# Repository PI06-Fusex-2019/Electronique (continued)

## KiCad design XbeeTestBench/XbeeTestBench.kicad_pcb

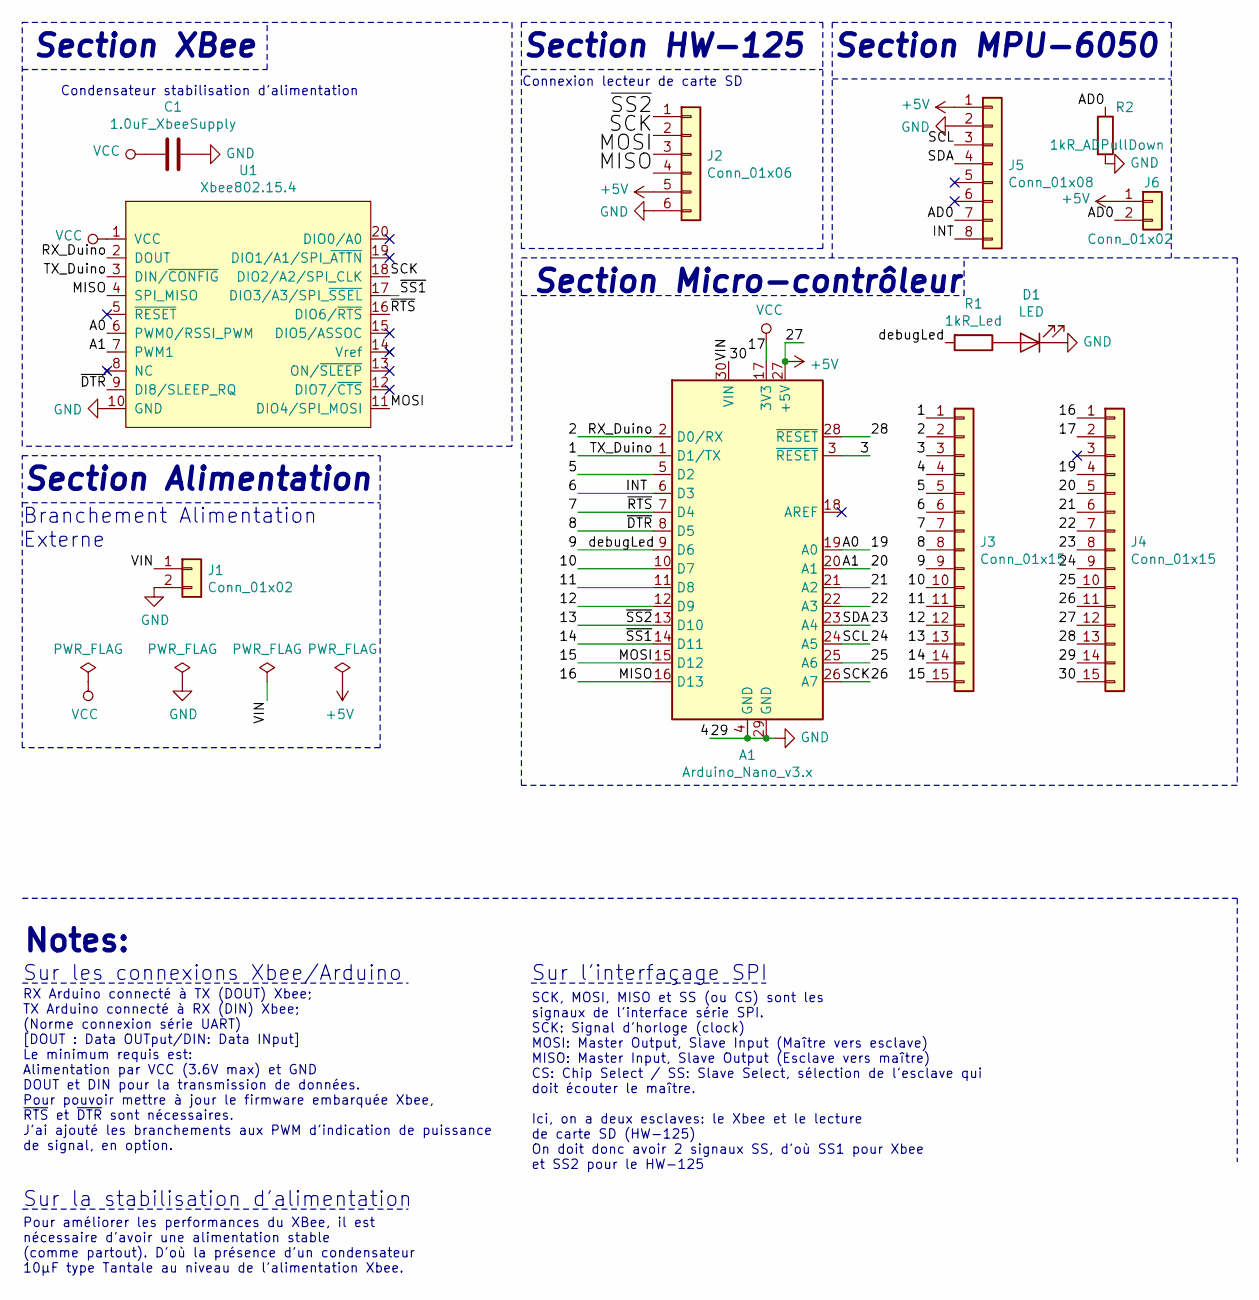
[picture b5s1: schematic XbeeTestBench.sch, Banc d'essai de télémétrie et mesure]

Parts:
A1: Arduino_Nano_v3.x; Arduino_Nano
C1: 1.0uF_XbeeSupply; C_1206_3216Metric_Pad1.42x1.75mm_HandSolder
D1: LED; LED_D5.0mm
J1: Conn_01x02; BatConn
J2: Conn_01x06; PinHeader_1x06_P2.54mm_Vertical
J3, J4: Conn_01x15; PinHeader_1x15_P2.54mm_Vertical
J5: Conn_01x08; PinSocket_1x08_P2.54mm_Vertical
J6: Conn_01x02; PinSocket_1x02_P2.54mm_Horizontal
R1: 1kR_Led; R_1206_3216Metric_Pad1.42x1.75mm_HandSolder
R2: 1kR_ADPullDown; R_1206_3216Metric_Pad1.42x1.75mm_HandSolder
U1: Xbee802.15.4; XBEE-20_THT

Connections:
+5V: A1.27 (+5V), J2.5, J4.12, J5.1, J6.1
/1: A1.1 (D1/TX), J3.1, U1.3 (DIN/~CONFIG)
/2: A1.2 (D0/RX), J3.2, U1.2 (DOUT)
/3: A1.3 (~RESET), J3.3
/5: A1.5 (D2), J3.5
/6: A1.6 (D3), J3.6, J5.8
/7: A1.7 (D4), J3.7, U1.16 (DIO6/~RTS)
/8: A1.8 (D5), J3.8, U1.9 (DI8/SLEEP_RQ)
/9: A1.9 (D6), J3.9, R1.2
/10: A1.10 (D7), J3.10
/11: A1.11 (D8), J3.11
/12: A1.12 (D9), J3.12
/13: A1.13 (D10), J2.1, J3.13
/14: A1.14 (D11), J3.14, U1.17 (DIO3/A3/SPI_~SSEL)
/15: A1.15 (D12), J2.3, J3.15, U1.11 (DIO4/SPI_MOSI)
/16: A1.16 (D13), J2.4, J4.1, U1.4 (SPI_MISO)
/19: A1.19 (A0), J4.4, U1.6 (PWM0/RSSI_PWM)
/20: A1.20 (A1), J4.5, U1.7 (PWM1)
/21: A1.21 (A2), J4.6
/22: A1.22 (A3), J4.7
/23: A1.23 (A4), J4.8, J5.4
/24: A1.24 (A5), J4.9, J5.3
/25: A1.25 (A6), J4.10
/26: A1.26 (A7), J2.2, J4.11, U1.18 (DIO2/A2/SPI_CLK)
/28: A1.28 (~RESET), J4.13
/30: A1.30 (VIN), J1.1, J4.15
/AD0: J5.7, J6.2, R2.1
GND: A1.4 (GND), A1.29 (GND), C1.1, D1.1 (K), J1.2, J2.6, J3.4, J4.14, J5.2, R2.2, U1.10 (GND)
unnamed: D1.2 (A), R1.1
VCC: A1.17 (3V3), C1.2, J4.2, U1.1 (VCC)

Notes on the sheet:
RX Arduino connecté à TX (DOUT) Xbee; TX Arduino connecté à RX (DIN) Xbee; (Norme connexion série UART) [DOUT : Data OUTput/DIN: Data INput] Le minimum requis est: Alimentation par VCC (3.6V max) et GND DOUT et DIN pour la transmission de données. Pour pouvoir mettre à jour le firmware embarquée Xb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
Sur les connexions Xbee/Arduino
Notes:
Pour améliorer les performances du XBee, il est nécessaire d'avoir une alimentation stable (comme partout). D'où la présence d'un condensateur 10µF type Tantale au niveau de l'alimentation Xbee.
Sur la stabilisation d'alimentation
Condensateur stabilisation d'alimentation
Branchement Alimentation Externe
Sur l'interfaçage SPI
SCK, MOSI, MISO et SS (ou CS) sont les signaux de l'interface série SPI. SCK: Signal d'horloge (clock) MOSI: Master Output, Slave Input (Maître vers esclave) MISO: Master Input, Slave Output (Esclave vers maître) CS: Chip Select / SS: Slave Select, sélection de l'esclave qui doit écouter le maître.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
Section XBee
Section HW-125
Connexion lecteur de carte SD
Section Alimentation
Section Micro-contrôleur
Section MPU-6050

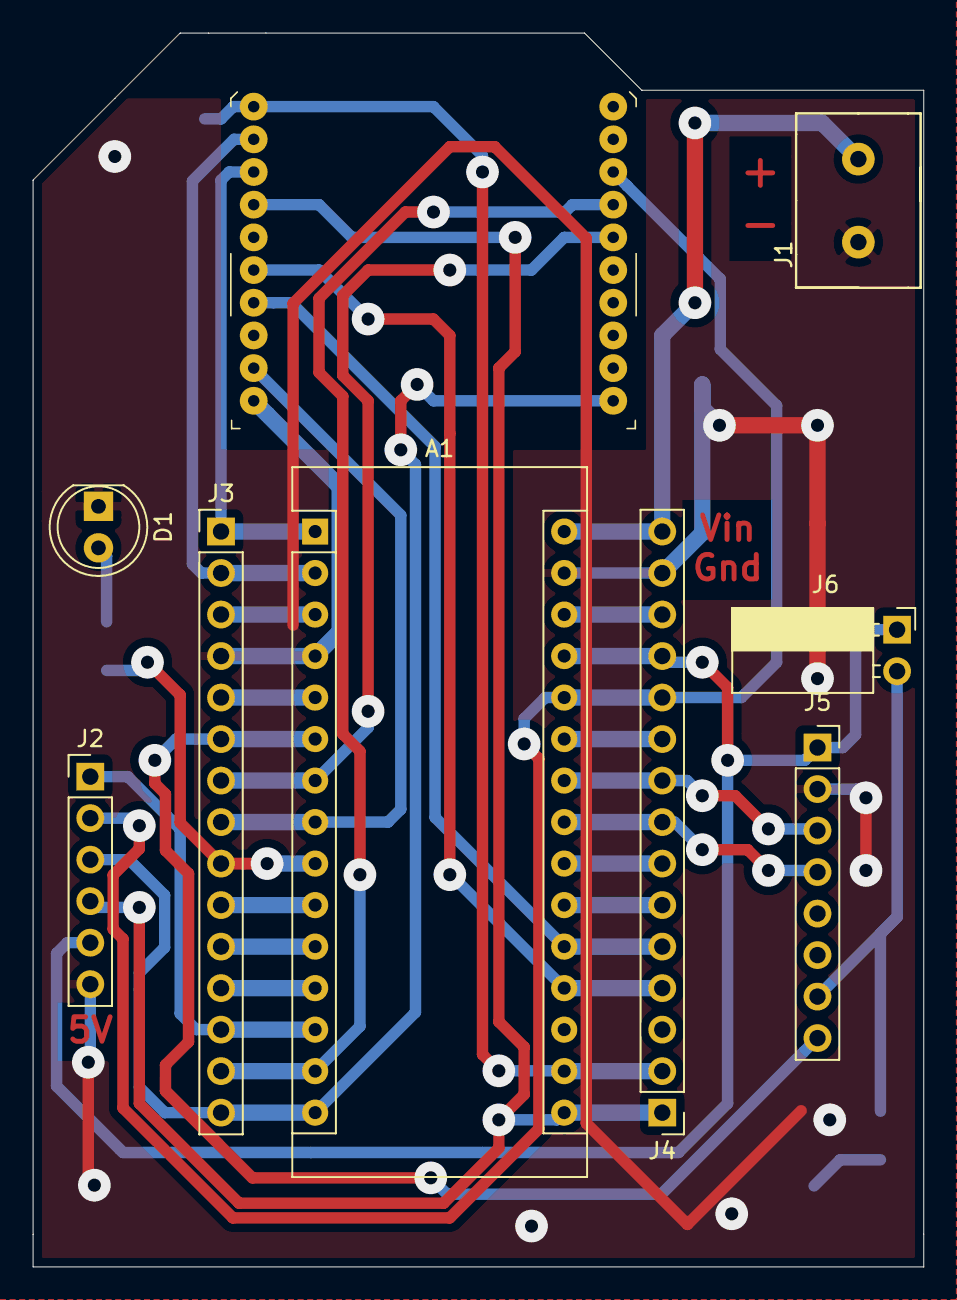
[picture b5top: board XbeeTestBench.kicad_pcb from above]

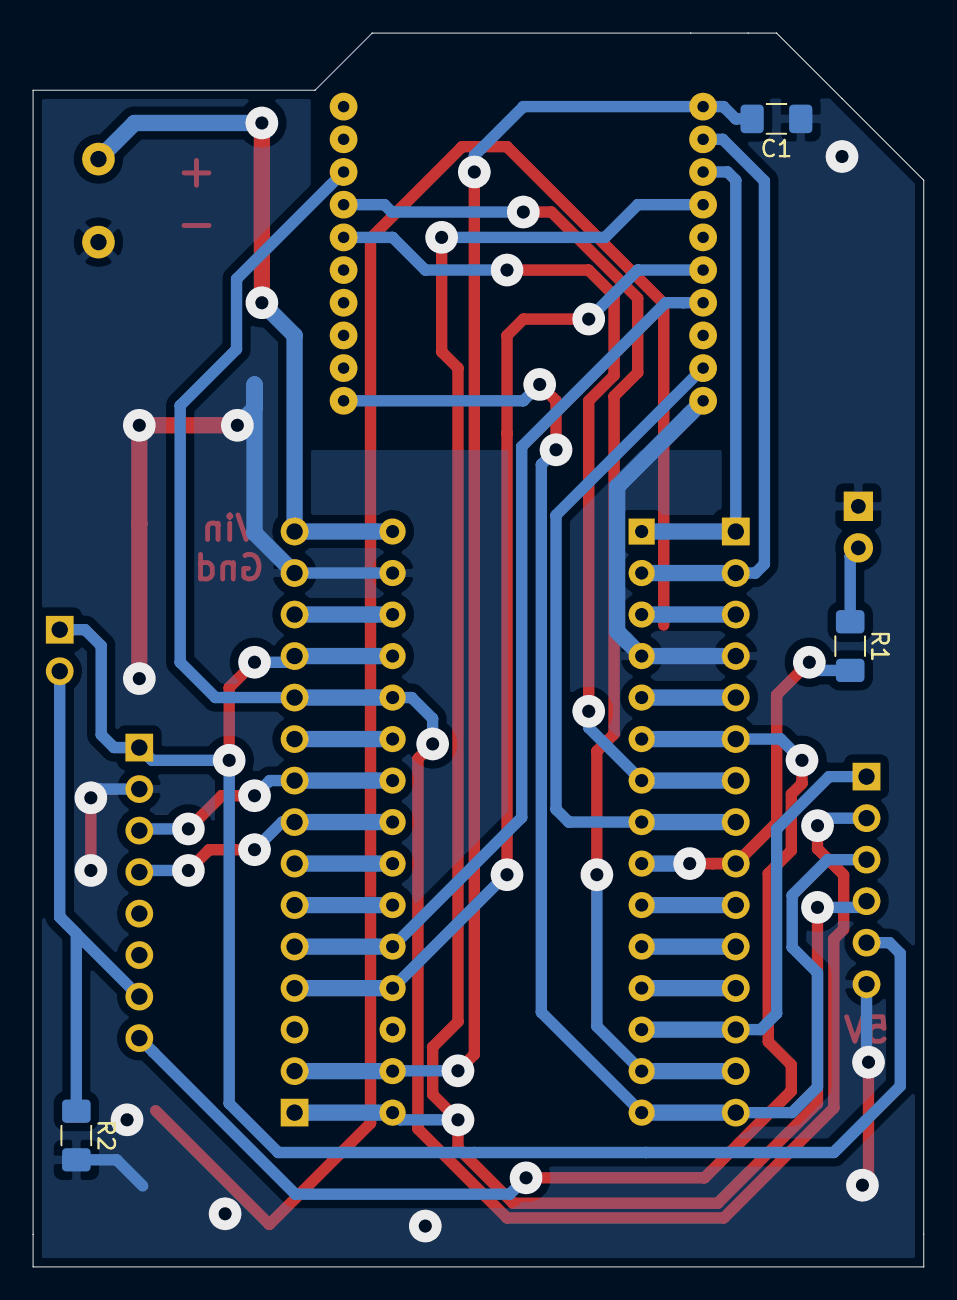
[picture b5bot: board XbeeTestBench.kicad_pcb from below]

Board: 2 copper layers, 54.5 x 75.5 mm, 12 parts (3 on the bottom side), 30 nets.

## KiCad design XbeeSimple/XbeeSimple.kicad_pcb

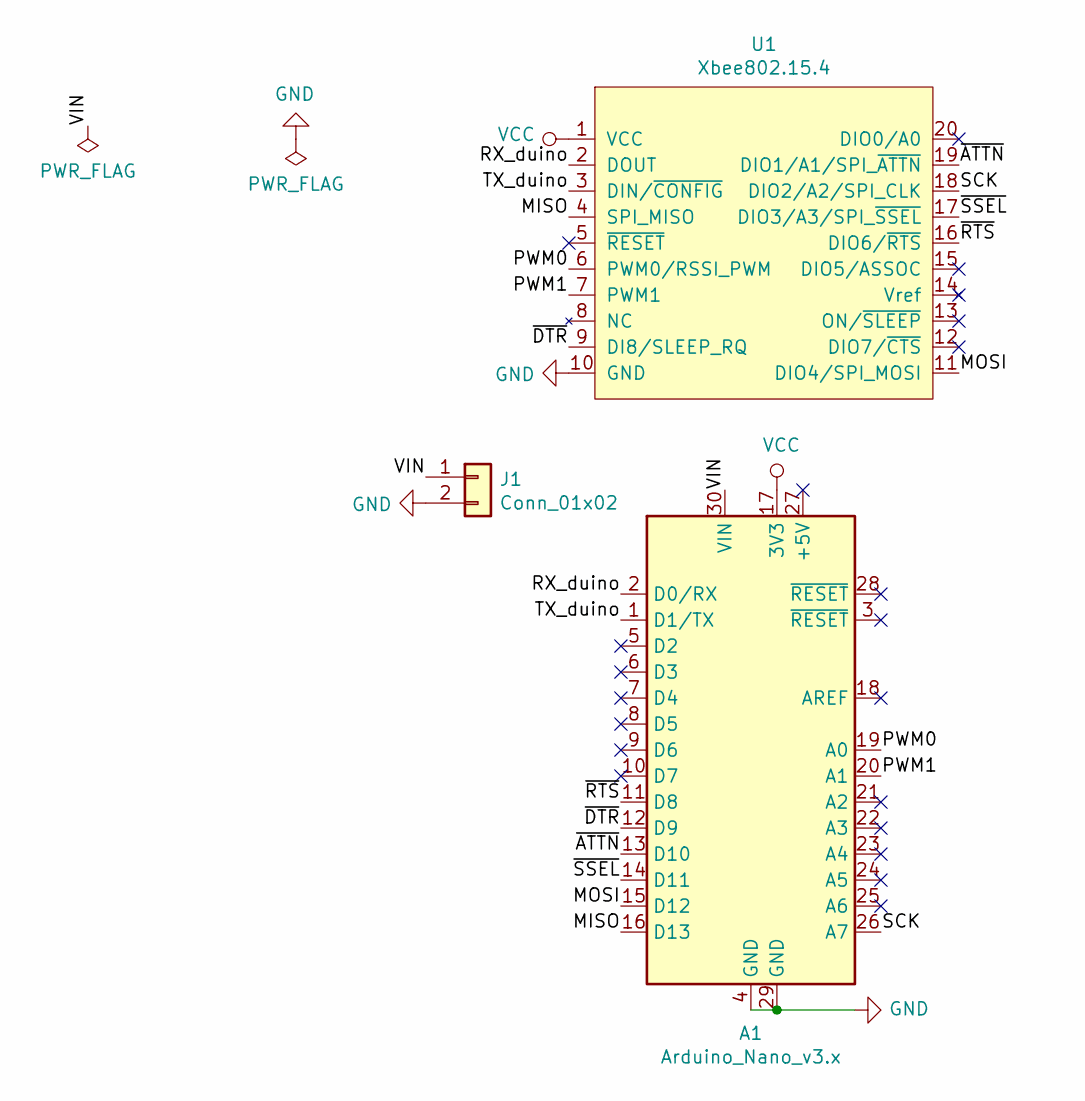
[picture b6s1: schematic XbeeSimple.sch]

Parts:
A1: Arduino_Nano_v3.x; Arduino_Nano
J1: Conn_01x02; BatConn
U1: Xbee802.15.4; XBEE-20_THT

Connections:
/MISO: A1.16 (D13), U1.4 (SPI_MISO)
/MOSI: A1.15 (D12), U1.11 (DIO4/SPI_MOSI)
/PWM0: A1.19 (A0), U1.6 (PWM0/RSSI_PWM)
/PWM1: A1.20 (A1), U1.7 (PWM1)
/RX_duino: A1.2 (D0/RX), U1.2 (DOUT)
/SCK: A1.26 (A7), U1.18 (DIO2/A2/SPI_CLK)
/TX_duino: A1.1 (D1/TX), U1.3 (DIN/~CONFIG)
/VIN: A1.30 (VIN), J1.1
/~ATTN: A1.13 (D10), U1.19 (DIO1/A1/SPI_~ATTN)
/~DTR: A1.12 (D9), U1.9 (DI8/SLEEP_RQ)
/~RTS: A1.11 (D8), U1.16 (DIO6/~RTS)
/~SSEL: A1.14 (D11), U1.17 (DIO3/A3/SPI_~SSEL)
GND: A1.4 (GND), A1.29 (GND), J1.2, U1.10 (GND)
VCC: A1.17 (3V3), U1.1 (VCC)

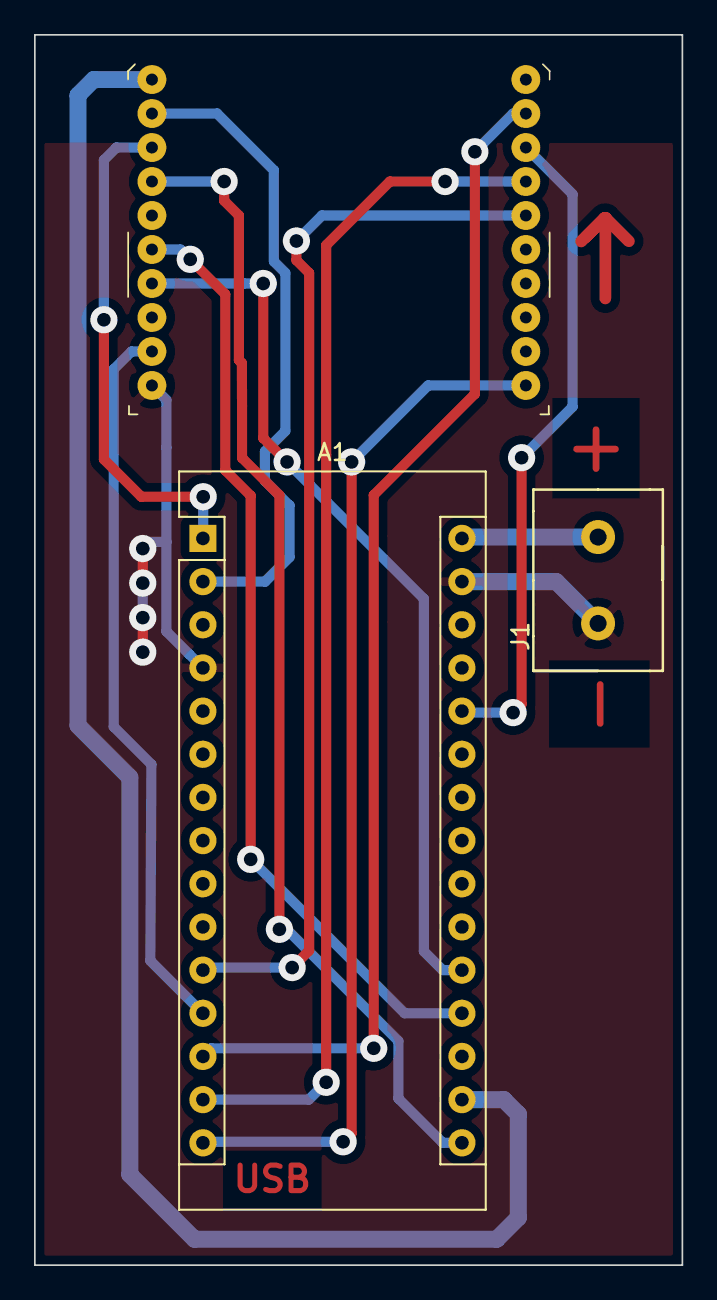
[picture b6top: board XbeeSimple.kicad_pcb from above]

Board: 2 copper layers, 38.1 x 72.4 mm, 3 parts (0 on the bottom side), 14 nets.

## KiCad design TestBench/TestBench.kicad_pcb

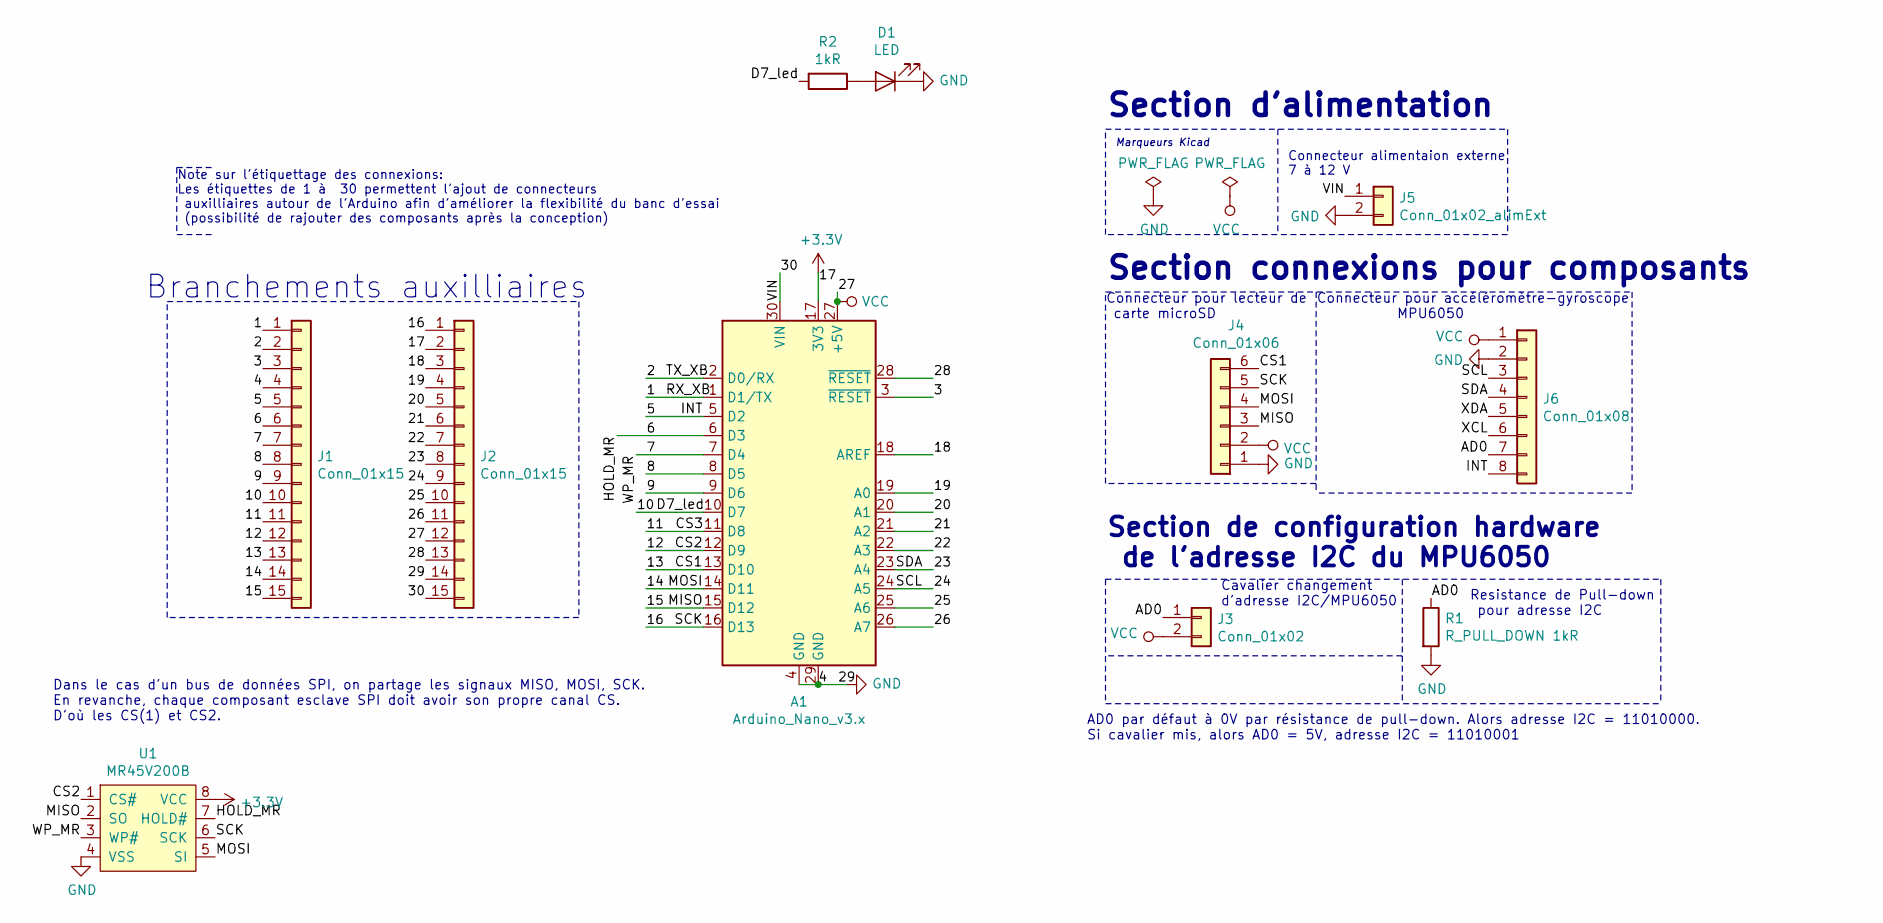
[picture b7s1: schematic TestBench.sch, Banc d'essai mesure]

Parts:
A1: Arduino_Nano_v3.x; Arduino_Nano
D1: LED; LED_D5.0mm
J1, J2: Conn_01x15; PinHeader_1x15_P2.54mm_Vertical
J3: Conn_01x02; PinHeader_1x02_P2.54mm_Vertical
J4: Conn_01x06; PinHeader_1x06_P2.54mm_Vertical
J5: Conn_01x02_alimExt; BatConn
J6: Conn_01x08; PinHeader_1x08_P2.54mm_Vertical
R1: R_PULL_DOWN 1kR; R_1206_3216Metric_Pad1.42x1.75mm_HandSolder
R2: 1kR; R_1206_3216Metric_Pad1.42x1.75mm_HandSolder
U1: MR45V200B; DIP-8_W7.62mm_LongPads

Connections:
+3V3: A1.17 (3V3), J2.2, U1.8 (VCC)
/1: A1.1 (D1/TX), J1.1
/2: A1.2 (D0/RX), J1.2
/3: A1.3 (~RESET), J1.3
/5: A1.5 (D2), J1.5, J6.8
/6: A1.6 (D3), J1.6, U1.7 (HOLD#)
/7: A1.7 (D4), J1.7, U1.3 (WP#)
/8: A1.8 (D5), J1.8
/9: A1.9 (D6), J1.9
/10: A1.10 (D7), J1.10, R2.2
/11: A1.11 (D8), J1.11
/12: A1.12 (D9), J1.12, U1.1 (CS#)
/13: A1.13 (D10), J1.13, J4.6
/14: A1.14 (D11), J1.14, J4.4, U1.5 (SI)
/15: A1.15 (D12), J1.15, J4.3, U1.2 (SO)
/16: A1.16 (D13), J2.1, J4.5, U1.6 (SCK)
/18: A1.18 (AREF), J2.3
/19: A1.19 (A0), J2.4
/20: A1.20 (A1), J2.5
/21: A1.21 (A2), J2.6
/22: A1.22 (A3), J2.7
/23: A1.23 (A4), J2.8, J6.4
/24: A1.24 (A5), J2.9, J6.3
/25: A1.25 (A6), J2.10
/26: A1.26 (A7), J2.11
/28: A1.28 (~RESET), J2.13
/30: A1.30 (VIN), J2.15, J5.1
/AD0: J3.1, J6.7, R1.1
/XCL: J6.6
/XDA: J6.5
GND: A1.4 (GND), A1.29 (GND), D1.1 (K), J1.4, J2.14, J4.1, J5.2, J6.2, R1.2, U1.4 (VSS)
unnamed: D1.2 (A), R2.1
VCC: A1.27 (+5V), J2.12, J3.2, J4.2, J6.1

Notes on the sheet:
Resistance de Pull-down pour adresse I2C
Cavalier changement d'adresse I2C/MPU6050
Section de configuration hardware de l'adresse I2C du MPU6050
AD0 par défaut à 0V par résistance de pull-down. Alors adresse I2C = 11010000. Si cavalier mis, alors AD0 = 5V, adresse I2C = 11010001
Connecteur pour accéléromètre-gyroscope MPU6050
Connecteur pour lecteur de carte microSD
Section connexions pour composants
Connecteur alimentaion externe 7 à 12 V
Marqueurs Kicad
Section d'alimentation
Note sur l'étiquettage des connexions: Les étiquettes de 1 à 30 permettent l'ajout de connecteurs auxilliaires autour de l'Arduino afin d'améliorer la flexibilité du banc d'essai (possibilité de rajouter des composants après la conception)
Branchements auxilliaires
Dans le cas d'un bus de données SPI, on partage les signaux MISO, MOSI, SCK. En revanche, chaque composant esclave SPI doit avoir son propre canal CS. D'où les CS(1) et CS2.

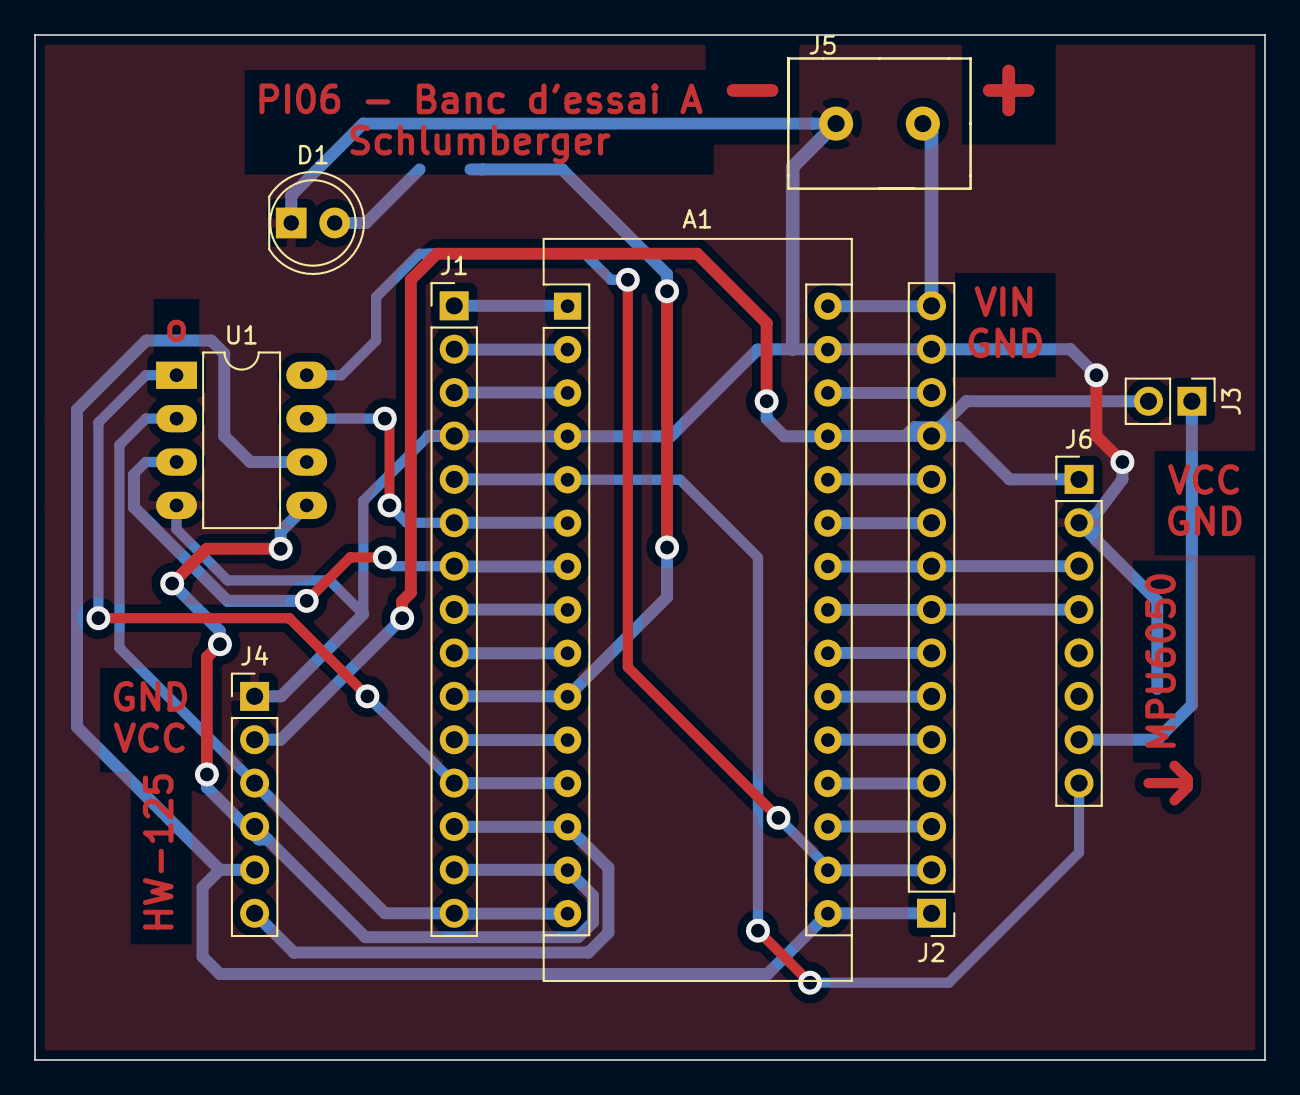
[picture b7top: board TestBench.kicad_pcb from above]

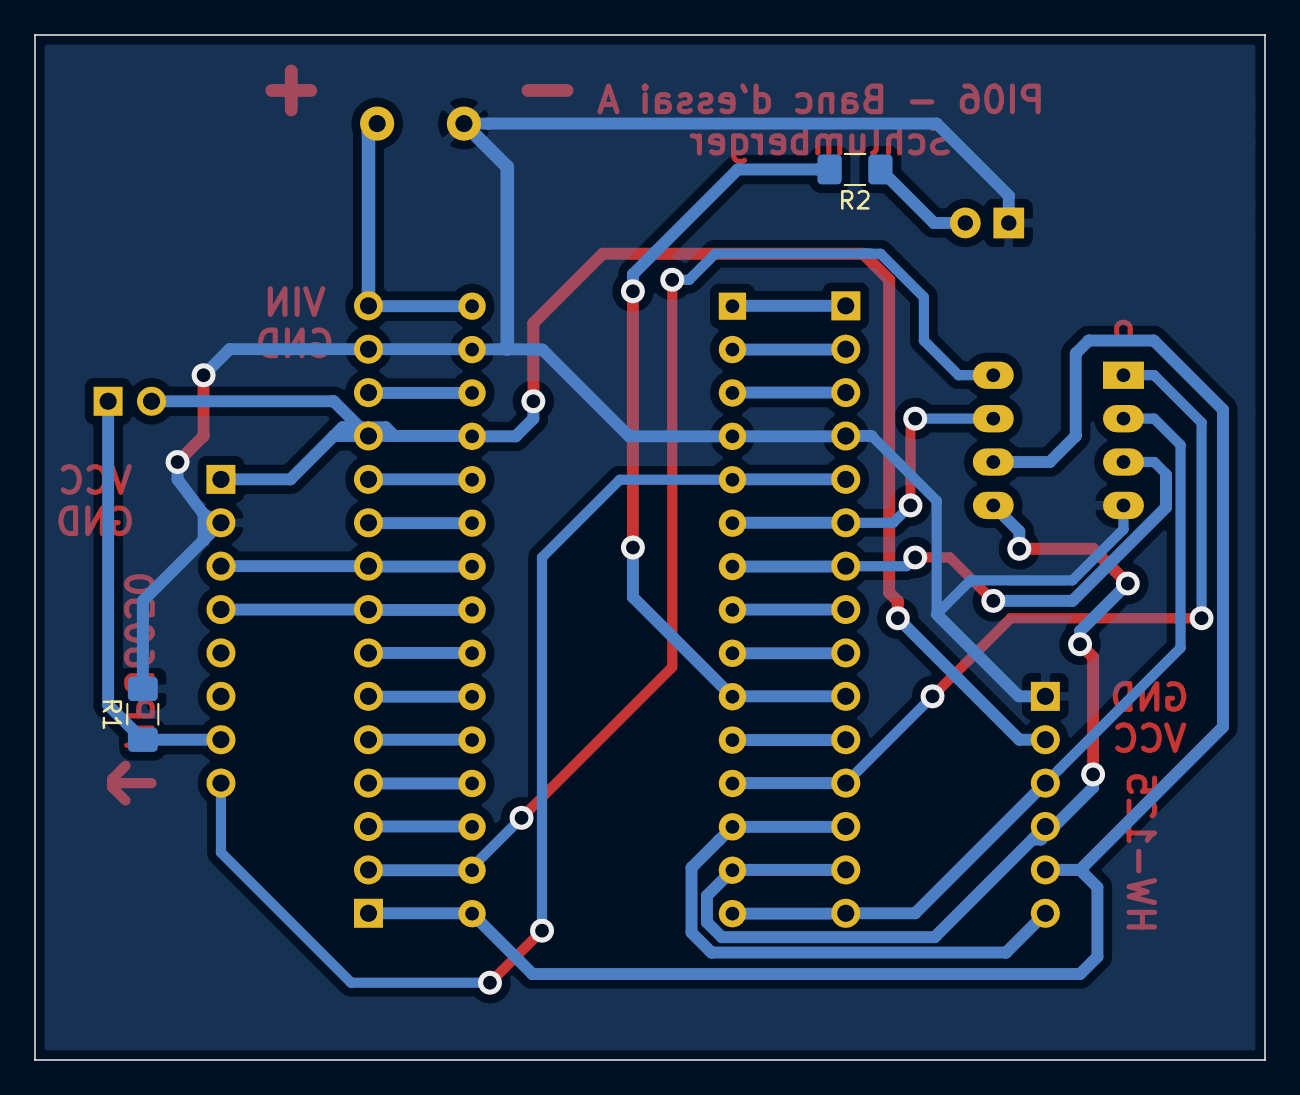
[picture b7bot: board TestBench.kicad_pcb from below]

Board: 2 copper layers, 72.0 x 60.0 mm, 11 parts (2 on the bottom side), 31 nets.

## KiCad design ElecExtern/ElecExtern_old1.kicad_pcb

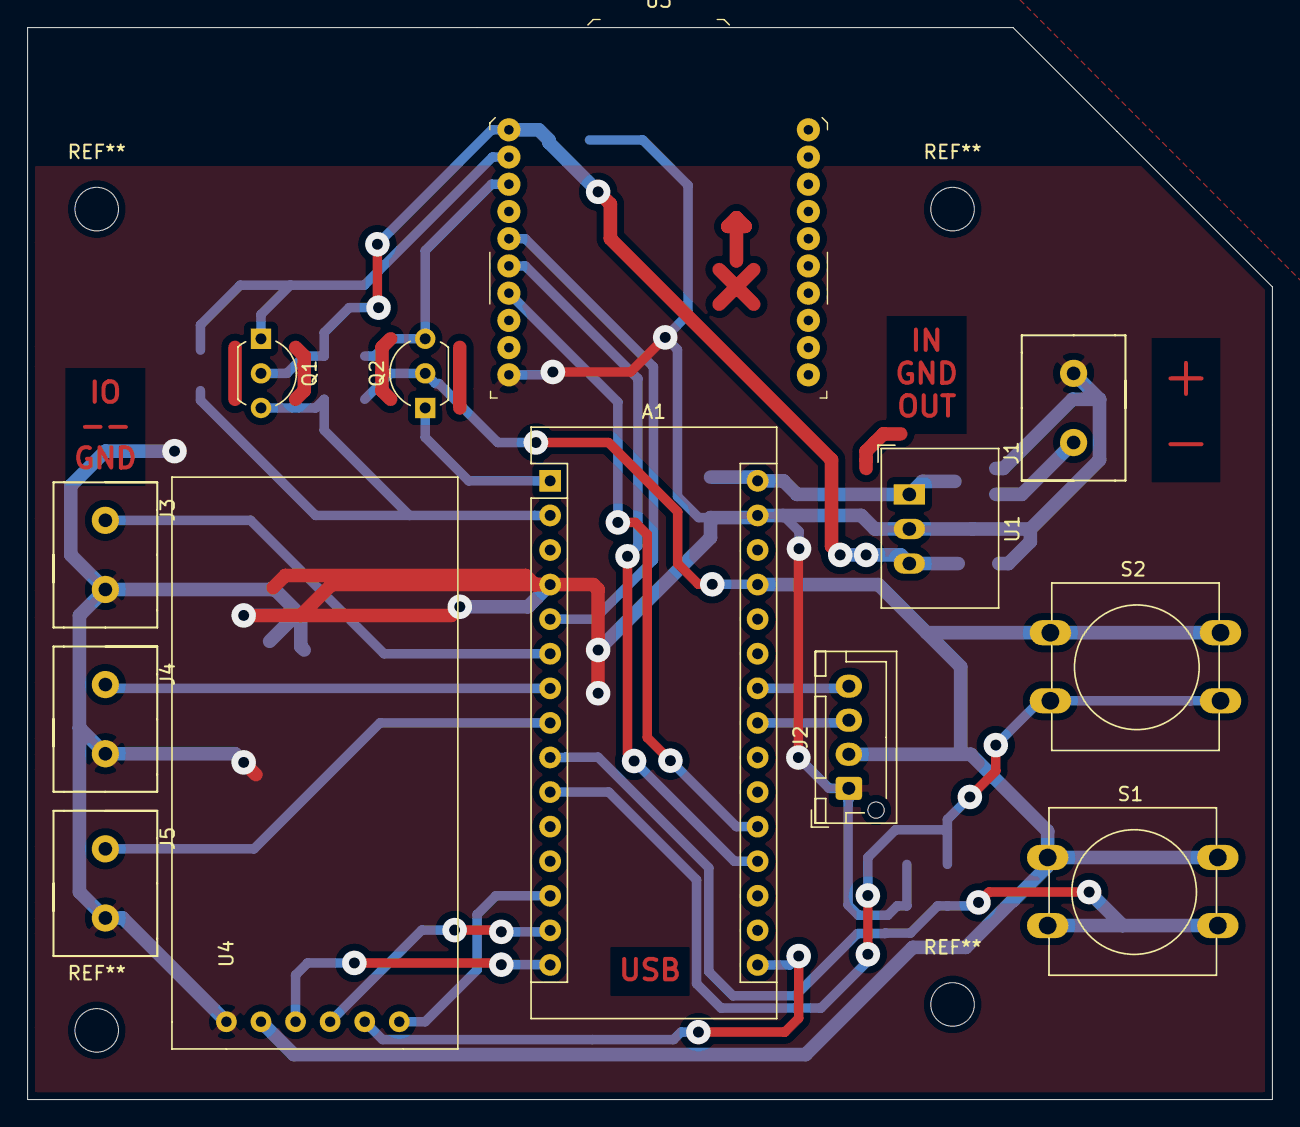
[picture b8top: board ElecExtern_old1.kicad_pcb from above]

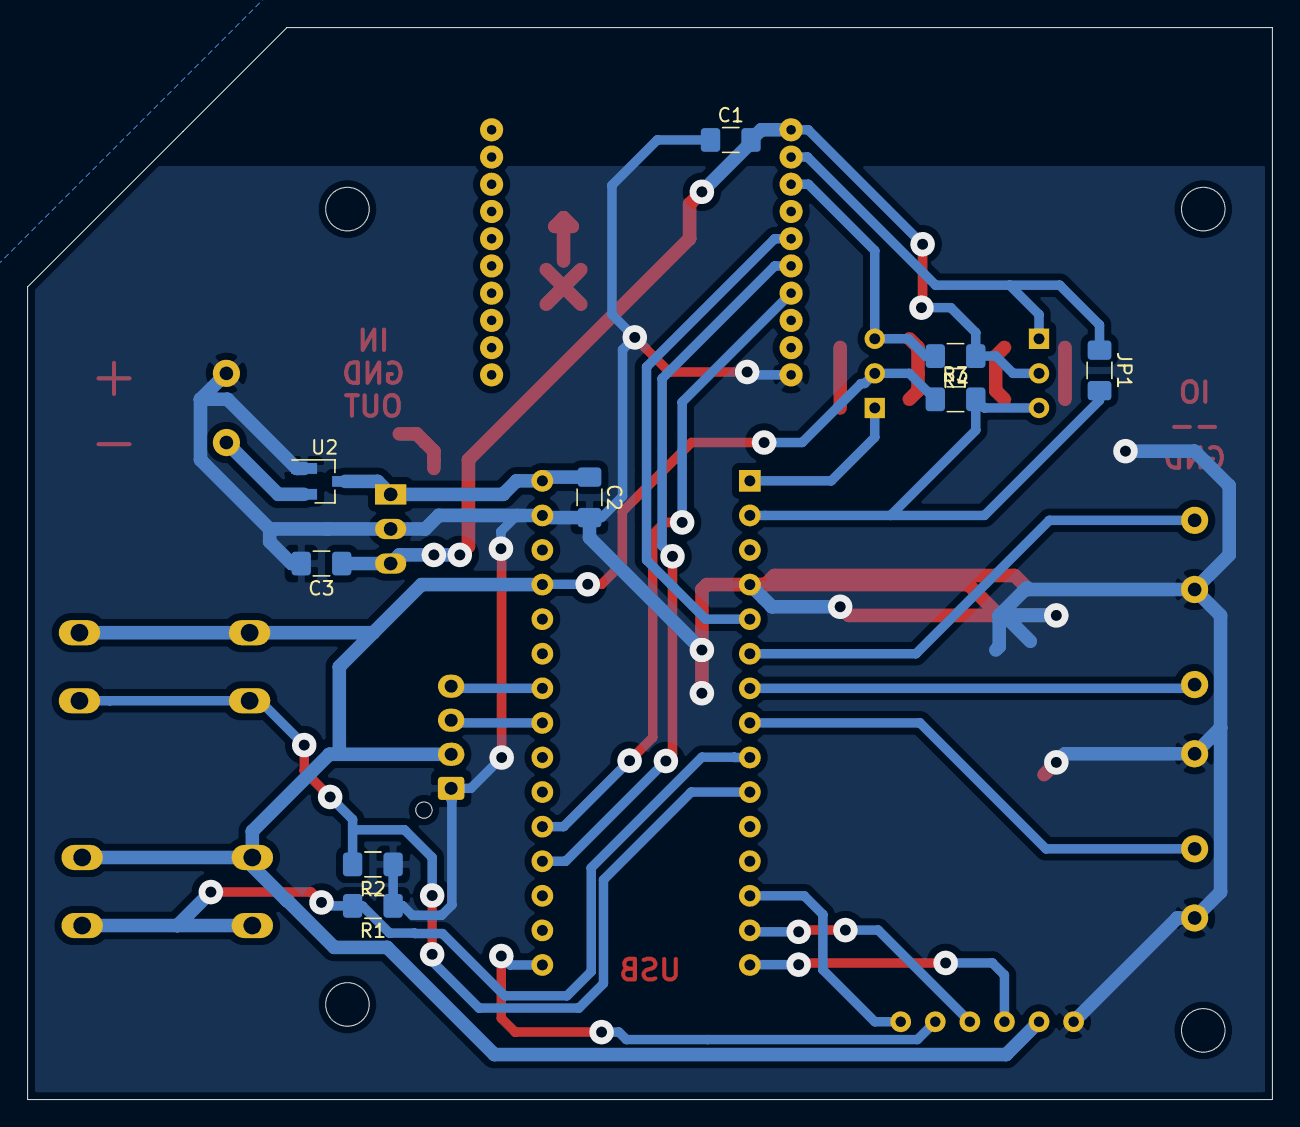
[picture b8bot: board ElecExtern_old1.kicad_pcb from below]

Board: 2 copper layers, 91.4 x 78.7 mm, 22 parts (9 on the bottom side), 23 nets.

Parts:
A1: Arduino_Nano_v3.x; Arduino_Nano
C1, C3: 10uF; C_1206_3216Metric_Pad1.42x1.75mm_HandSolder
C2: C; C_1206_3216Metric_Pad1.42x1.75mm_HandSolder
J1, J3, J4, J5: Conn_01x02; BatConn
J2: Conn_01x04; JST_XH_B4B-XH-AM_1x04_P2.50mm_Vertical
JP1: SolderJumper_2_Open; R_1206_3216Metric_Pad1.42x1.75mm_HandSolder
Q1, Q2: Q_NMOS_DGS; TO-92L_Inline_Wide
R1, R2: 1kR pull-down; R_1206_3216Metric_Pad1.42x1.75mm_HandSolder
R3, R4: 1kR pull-up; R_1206_3216Metric_Pad1.42x1.75mm_HandSolder
S1, S2: GPTS203211B; SW_PUSH-12mm
U1: R-78C3.3-1.0; Converter_DCDC_RECOM_R-78E-0.5_THT
U2: PMOS; SOT-23_Handsoldering
U3: Xbee802.15.4; XBEE-20_THT
U4: SD_card; HW-125

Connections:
+3V3: C1.2, C3.1, Q1.2, R4.1, U1.3, U3.1
+5V: A1.27, J2.2, Q2.2, R3.1, S1.1, S2.1, U4.2
+12V: A1.30, C2.1, U1.1, U2.2
/Bouton1_IN: A1.9, R1.2, S1.2
/Bouton2_IN: A1.10, R2.2, S2.2
/DIN: Q2.1, R4.2, U3.3
/DOUT: JP1.1, Q1.3, U3.2
/IO1: A1.6, J3.2
/IO2: A1.7, J4.2
/IO3: A1.8, J5.2
/MISO: A1.15, U4.3
/MOSI: A1.14, U4.4
/PWM0_XBEE: A1.19, U3.6
/PWM1_XBEE: A1.20, U3.7
/RX_Duino: A1.2, JP1.2, Q1.1, R3.2
/SCK: A1.16, U4.5
/SCL: A1.24, J2.4
/SDA: A1.23, J2.3
/TX_Duino: A1.1, Q2.3
/Xbee-reset: A1.5, U3.5
/~CS: A1.13, U4.6
GND: A1.4, A1.29, C1.1, C2.2, C3.2, J1.1, J2.1, J3.1, J4.1, J5.1, R1.1, R2.1, U1.2, U2.1, U3.10, U4.1
unnamed: J1.2, U2.3

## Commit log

2019-12-02 Ajout des fichiers Banc D'essai
2019-12-02 Ajout PDF de preview du schéma banc d'essai
2019-12-02 Ajout PCB test bench Xbee
2019-12-12 Mise à jour + PDF Banc Xbee
2019-12-12 Mise a jour PDF
2020-01-18 MàJ des test bench, ajout des projets ElecExterne et ElecInterne
2020-02-05 Grosse mise à jour
2020-02-20 Sequenceur
